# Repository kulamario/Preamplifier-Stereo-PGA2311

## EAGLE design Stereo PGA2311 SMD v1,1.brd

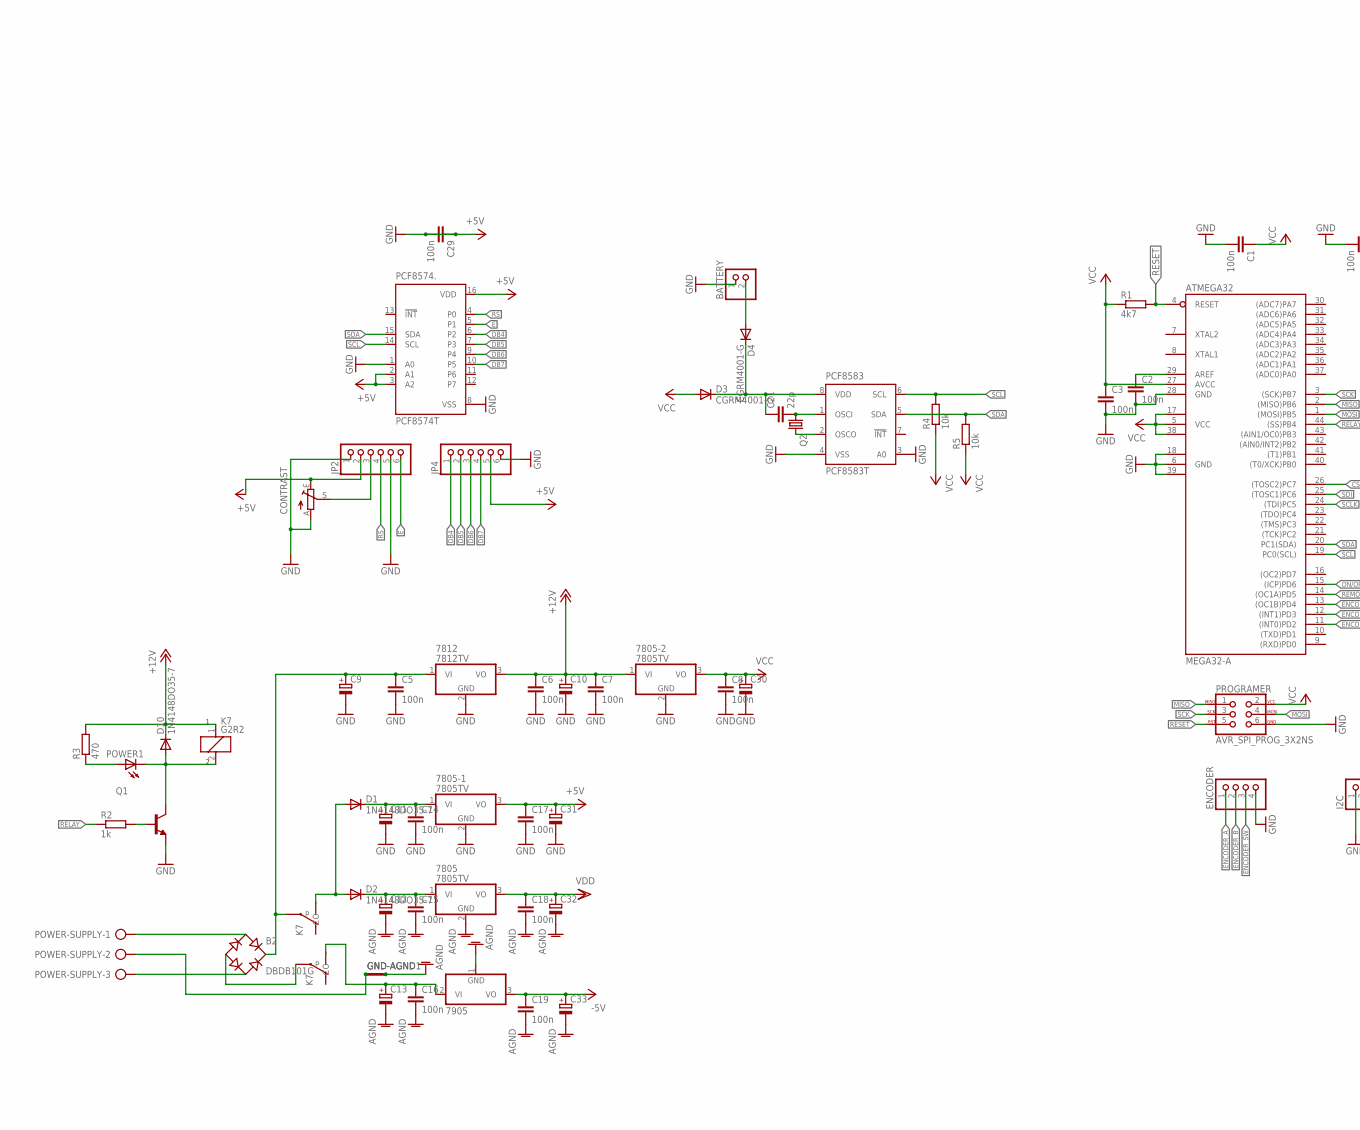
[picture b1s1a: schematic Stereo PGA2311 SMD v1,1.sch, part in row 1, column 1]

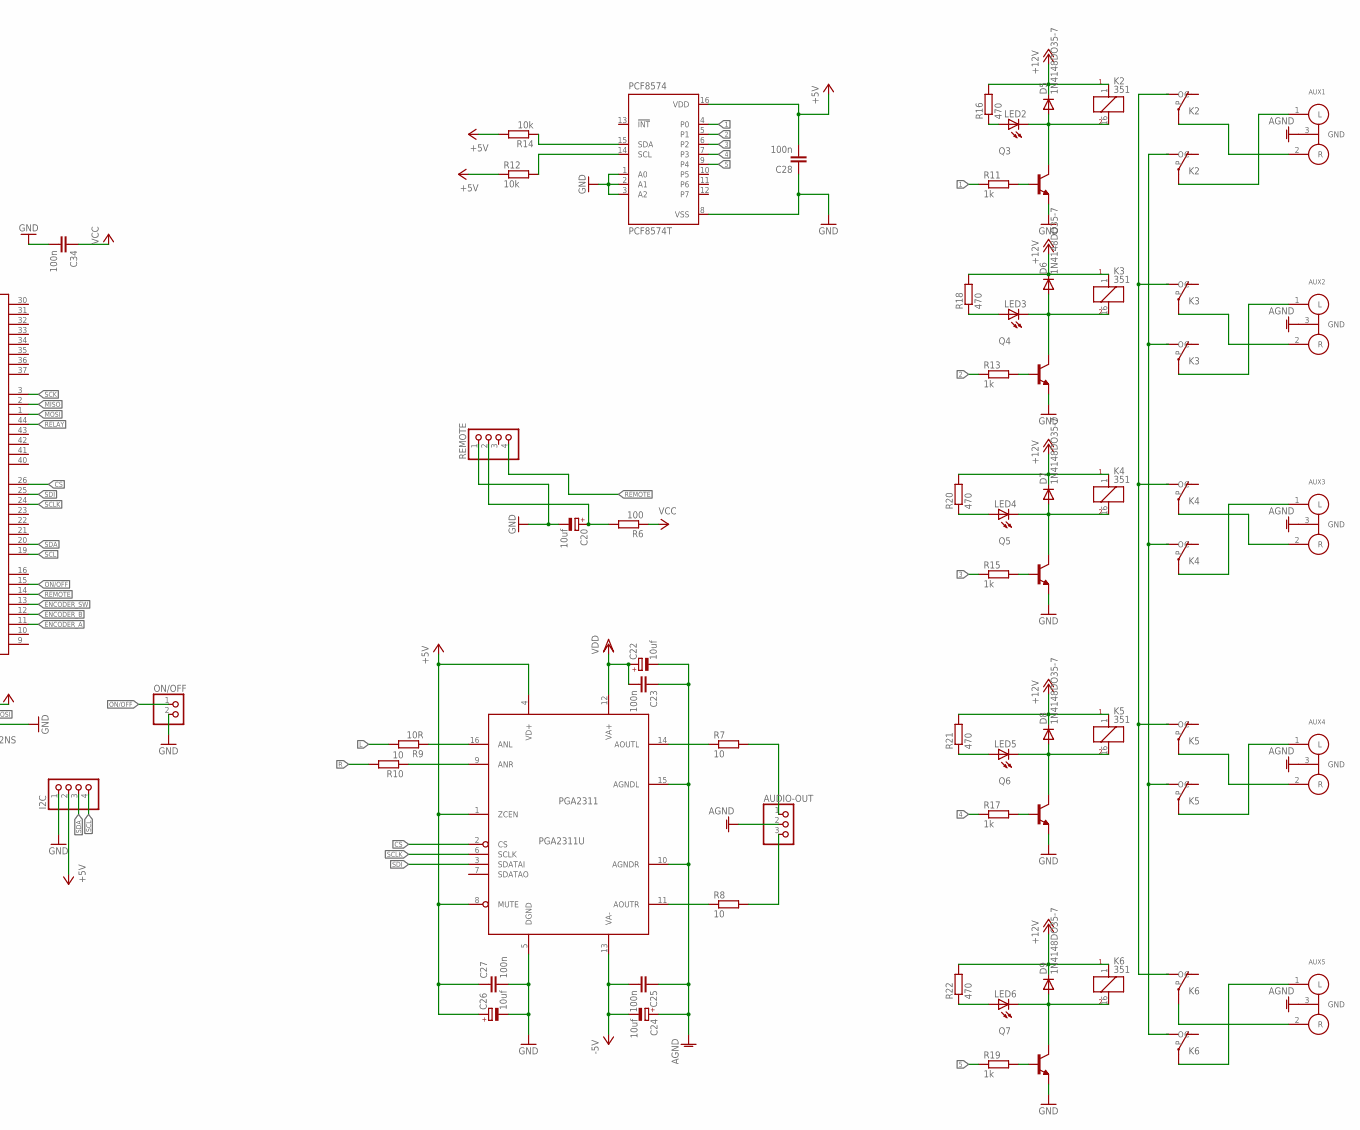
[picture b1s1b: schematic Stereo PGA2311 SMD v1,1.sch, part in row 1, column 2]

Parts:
7805, 7805-1, 7805-2: 7805TV; TO220V
7812: 7812TV; TO220V
7905: 79; TO220V
ATMEGA32: MEGA32-A; TQFP44
AUDIO-OUT: PINHD-1X3; 1X03
AUX1, AUX2, AUX3, AUX4, AUX5: RCA-EBAY
B2: DBDB101G; DB
BATTERY: PINHD-1X2; 1X02
C1: 100n; C0805
C2, C3, C23, C25, C27, C28, C29, C34: 100n; C0603
C5, C6, C7, C8, C14, C15, C16, C17, C18, C19: 100n; C025-030X050
C9, C10, C11, C12, C13, C30, C31, C32, C33: CPOL-EUE2.5-7; E2,5-7
C20: 10uf; E2-4
C21: 22p; C0603K
C22, C24, C26: 10uf; 153CLV-0505
CONTRAST: TRIM_EU-CA6V; CA6V
D1, D2, D5, D6, D7, D8, D9, D10: 1N4148DO35-7; DO35-7
D3, D4: CGRM4001-G; SOD-123_MINI-SMA
ENCODER: PINHD-1X4; 1X04
GND-AGND, GND-AGND1: SHORT-HT5; SHORT_TOP-50
I2C: PINHD-1X4; 1X04
JP2, JP4: PINHD-1X6; 1X06
K2, K3, K4, K5, K6: 351
K7: G2R2
LED2, LED3, LED4, LED5, LED6: LEDCHIPLED_0805; CHIPLED_0805
ON/OFF: PINHD-1X2; 1X02
PCF8574, PCF8574.: PCF8574T; SO16W
PCF8583: PCF8583T; SO8-7_5
PGA2311: PGA2311U; SO16-1
POWER1: LEDCHIPLED_0805; CHIPLED_0805
POWER-SUPPLY: AK300/3
PROGRAMER: AVR_SPI_PROG_3X2NS; 2X3-NS
Q1, Q3, Q4, Q5, Q6, Q7: BC547A-NPN-TO92-CBE; TO92-CBE
Q2: CRYSTALTC26H; TC26H
R1: 4k7; R0603
R2, R11, R13, R15, R17, R19: 1k; R0603
R3, R16, R18, R20, R21, R22: 470; R0603
R4, R5, R12, R14: 10k; R0603
R6: 100; R0603
R7, R8, R10: 10; R0603
R9: 10R; R0603
REMOTE: PINHD-1X4; 1X04

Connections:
1: PCF8574.4 (P0), R11.1
2: PCF8574.5 (P1), R13.1
3: PCF8574.6 (P2), R15.1
4: PCF8574.7 (P3), R17.1
5: PCF8574.9 (P4), R19.1
+5V: 7805-1.3 (VO), C17.1, C26.+, C27.1, C28.2, C29.1, C29.2, C31.+, CONTRAST.E, I2C.2, JP2.2, JP4.5, PCF8574.16 (VDD), PCF8574..2 (A1), PCF8574..3 (A2), PCF8574..16 (VDD), PGA2311.1 (ZCEN), PGA2311.4 (VD+), PGA2311.8 (MUTE), R12.1, R14.2
+12V: 7805-2.1 (VI), 7812.3 (VO), C6.1, C7.1, C10.+, D5.C, D6.C, D7.C, D8.C, D9.C, D10.C, K2.1, K3.1, K4.1, K5.1, K6.1, K7.1, R3.2, R16.2, R18.2, R20.2, R21.2, R22.2
-5V: 7905.3 (VO), C19.1, C24.-, C25.2, C33.+, PGA2311.13 (VA-)
AGND: 7805.2 (GND), 7905.1 (GND), AUDIO-OUT.2, AUX1.3 (GND), AUX2.3 (GND), AUX3.3 (GND), AUX4.3 (GND), AUX5.3 (GND), C12.-, C13.-, C15.2, C16.2, C18.2, C19.2, C22.-, C23.1, C24.+, C25.1, C32.-, C33.-, GND-AGND.2, GND-AGND1.2, PGA2311.10 (AGNDR), PGA2311.15 (AGNDL)
CS: ATMEGA32.26 ((TOSC2)PC7), PGA2311.2 (CS)
DB4: JP4.1, PCF8574..6 (P2)
DB5: JP4.2, PCF8574..7 (P3)
DB6: JP4.3, PCF8574..9 (P4)
DB7: JP4.4, PCF8574..10 (P5)
E: JP2.6, PCF8574..5 (P1)
ENCODER_A: ATMEGA32.11 ((INT0)PD2), ENCODER.1
ENCODER_B: ATMEGA32.12 ((INT1)PD3), ENCODER.2
ENCODER_SW: ATMEGA32.13 ((OC1B)PD4), ENCODER.3
GND: 7805-1.2 (GND), 7805-2.2 (GND), 7812.2 (GND), ATMEGA32.6 (GND), ATMEGA32.18 (GND1), ATMEGA32.28 (GND), ATMEGA32.39 (GND2), BATTERY.1, C1.2, C2.2, C3.2, C5.2, C6.2, C7.2, C8.2, C9.-, C10.-, C11.-, C14.2, C17.2, C20.-, C26.-, C27.2, C28.1, C30.-, C31.-, C34.2, CONTRAST.A, ENCODER.4, GND-AGND.1, GND-AGND1.1, I2C.1, JP2.1, JP2.5, JP4.6, ON/OFF.2, PCF8574.1 (A0), PCF8574.2 (A1), PCF8574.3 (A2), PCF8574.8 (VSS), PCF8574..1 (A0), PCF8574..8 (VSS), PCF8583.3 (A0), PCF8583.4 (VSS), PGA2311.5 (DGND), POWER-SUPPLY.2, PROGRAMER.6, Q1.E, Q3.E, Q4.E, Q5.E, Q6.E, Q7.E, REMOTE.1
L: K2.S2 (O), K3.S2 (O), K4.S2 (O), K5.S2 (O), K6.S2 (O), R9.2
MISO: ATMEGA32.2 ((MISO)PB6), PROGRAMER.1
MOSI: ATMEGA32.1 ((MOSI)PB5), PROGRAMER.4
unnamed: B2.AC1, POWER-SUPPLY.1
unnamed: B2.AC2, POWER-SUPPLY.3
unnamed: ATMEGA32.29 (AREF), C2.1
unnamed: C21.2, PCF8583.1 (OSCI), Q2.1
unnamed: 7812.1 (VI), B2.+, C5.1, C9.+, K7.P2
unnamed: B2.-, K7.P1
unnamed: 7905.2 (VI), C13.+, C16.1, K7.S1 (O)
unnamed: D1.A, D2.A, K7.S2 (O)
unnamed: 7805.1 (VI), C12.+, C15.1, D2.C
unnamed: 7805-1.1 (VI), C11.+, C14.1, D1.C
unnamed: D10.A, K7.2, POWER1.C, Q1.C
unnamed: Q1.B, R2.2
unnamed: PCF8583.2 (OSCO), Q2.2
unnamed: C21.1, D3.C, D4.C, PCF8583.8 (VDD)
unnamed: BATTERY.2, D4.A
unnamed: PGA2311.11 (AOUTR), R8.1
unnamed: C20.+, R6.2, REMOTE.2
unnamed: PGA2311.16 (ANL), R9.1
unnamed: PGA2311.9 (ANR), R10.1
unnamed: PGA2311.14 (AOUTL), R7.1
unnamed: D5.A, K2.16 (2), LED2.C, Q3.C
unnamed: Q3.B, R11.2
unnamed: LED2.A, R16.1
unnamed: Q4.B, R13.2
unnamed: LED3.A, R18.1
unnamed: Q5.B, R15.2
unnamed: LED4.A, R20.1
unnamed: Q6.B, R17.2
unnamed: LED5.A, R21.1
unnamed: Q7.B, R19.2
unnamed: LED6.A, R22.1
unnamed: D6.A, K3.16 (2), LED3.C, Q4.C
unnamed: AUDIO-OUT.1, R7.2
unnamed: AUDIO-OUT.3, R8.2
unnamed: AUX5.1 (L), K6.P2
unnamed: AUX5.2 (R), K6.P1
unnamed: AUX4.1 (L), K5.P2
unnamed: AUX4.2 (R), K5.P1
unnamed: AUX3.2 (R), K4.P1
unnamed: AUX3.1 (L), K4.P2
unnamed: AUX2.1 (L), K3.P2
unnamed: AUX2.2 (R), K3.P1
unnamed: AUX1.1 (L), K2.P2
unnamed: AUX1.2 (R), K2.P1
unnamed: D7.A, K4.16 (2), LED4.C, Q5.C
unnamed: D8.A, K5.16 (2), LED5.C, Q6.C
unnamed: D9.A, K6.16 (2), LED6.C, Q7.C
unnamed: POWER1.A, R3.1
unnamed: CONTRAST.S, JP2.3
ON/OFF: ATMEGA32.15 ((ICP)PD6), ON/OFF.1
R: K2.S1 (O), K3.S1 (O), K4.S1 (O), K5.S1 (O), K6.S1 (O), R10.2
RELAY: ATMEGA32.44 ((SS)PB4), R2.1
REMOTE: ATMEGA32.14 ((OC1A)PD5), REMOTE.4
RESET: ATMEGA32.4 (RESET), PROGRAMER.5, R1.2
RS: JP2.4, PCF8574..4 (P0)
SCK: ATMEGA32.3 ((SCK)PB7), PROGRAMER.3
SCL: ATMEGA32.19 (PC0(SCL)), I2C.4, PCF8574.14 (SCL), PCF8574..14 (SCL), PCF8583.6 (SCL), R4.2, R12.2
SCLK: ATMEGA32.24 ((TDI)PC5), PGA2311.6 (SCLK)
SDA: ATMEGA32.20 (PC1(SDA)), I2C.3, PCF8574.15 (SDA), PCF8574..15 (SDA), PCF8583.5 (SDA), R5.2, R14.1
SDI: ATMEGA32.25 ((TOSC1)PC6), PGA2311.3 (SDATAI)
VCC: 7805-2.3 (VO), ATMEGA32.5 (VCC), ATMEGA32.17 (VCC1), ATMEGA32.27 (AVCC), ATMEGA32.38 (VCC2), C1.1, C3.1, C8.1, C30.+, C34.1, D3.A, PROGRAMER.2, R1.1, R4.1, R5.1, R6.1
VDD: 7805.3 (VO), C18.1, C22.+, C23.2, C32.+, PGA2311.12 (VA+)

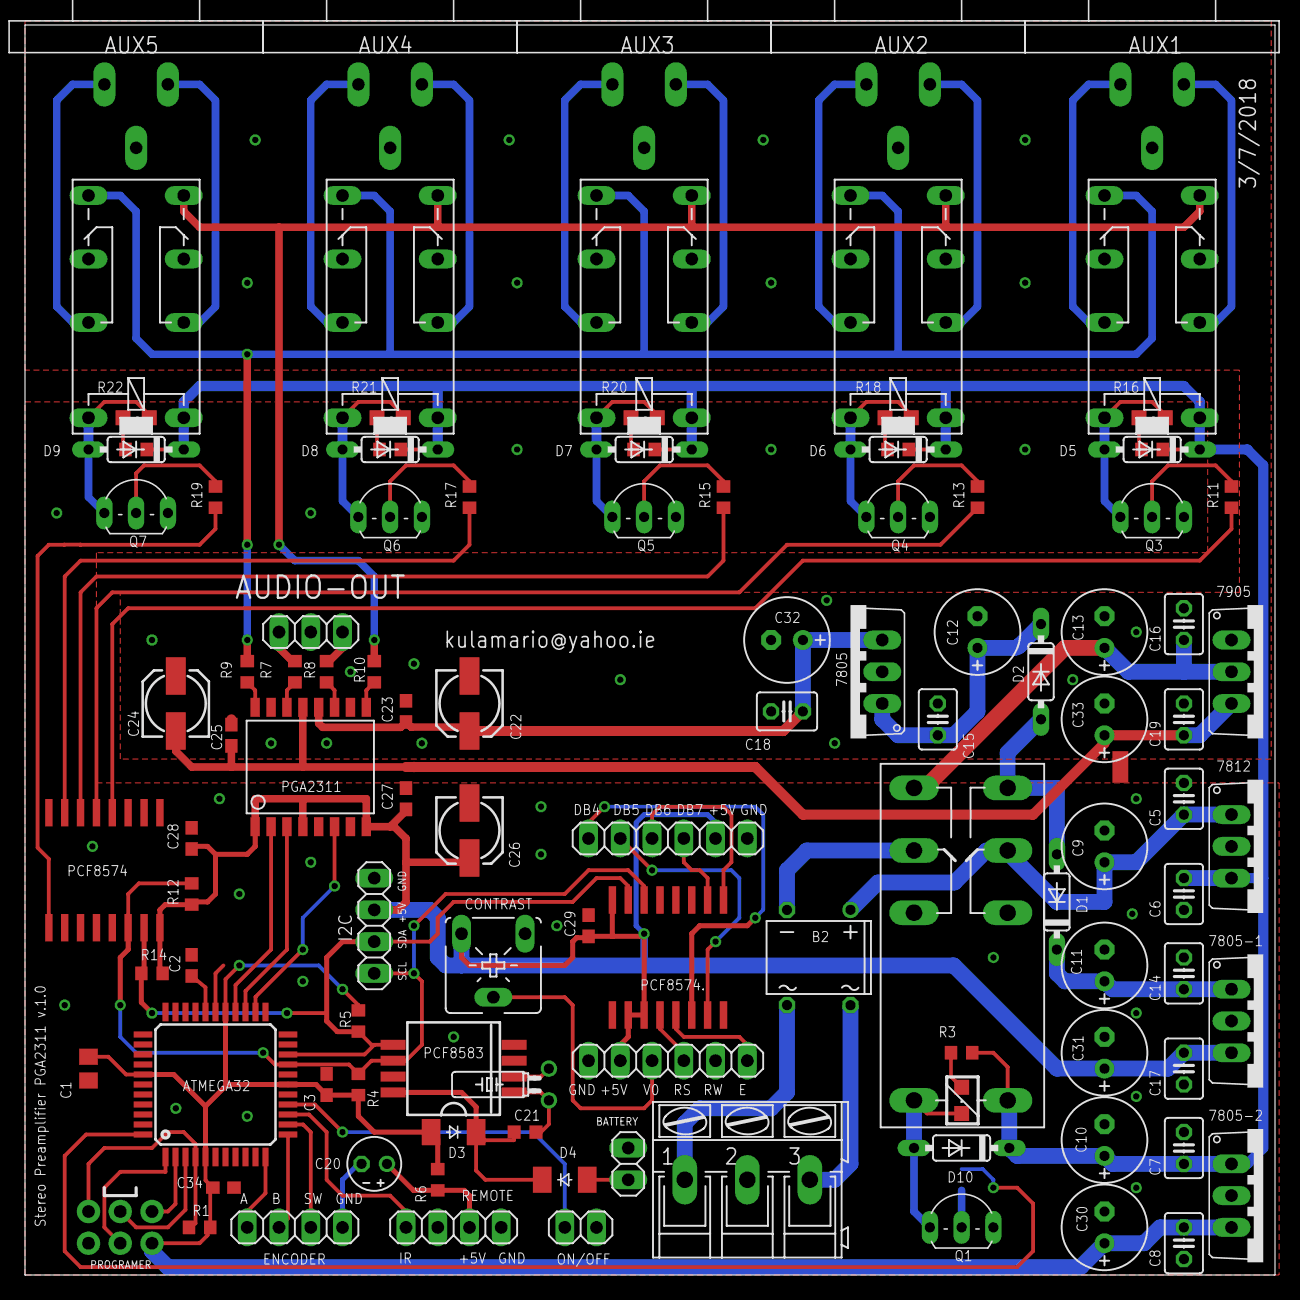
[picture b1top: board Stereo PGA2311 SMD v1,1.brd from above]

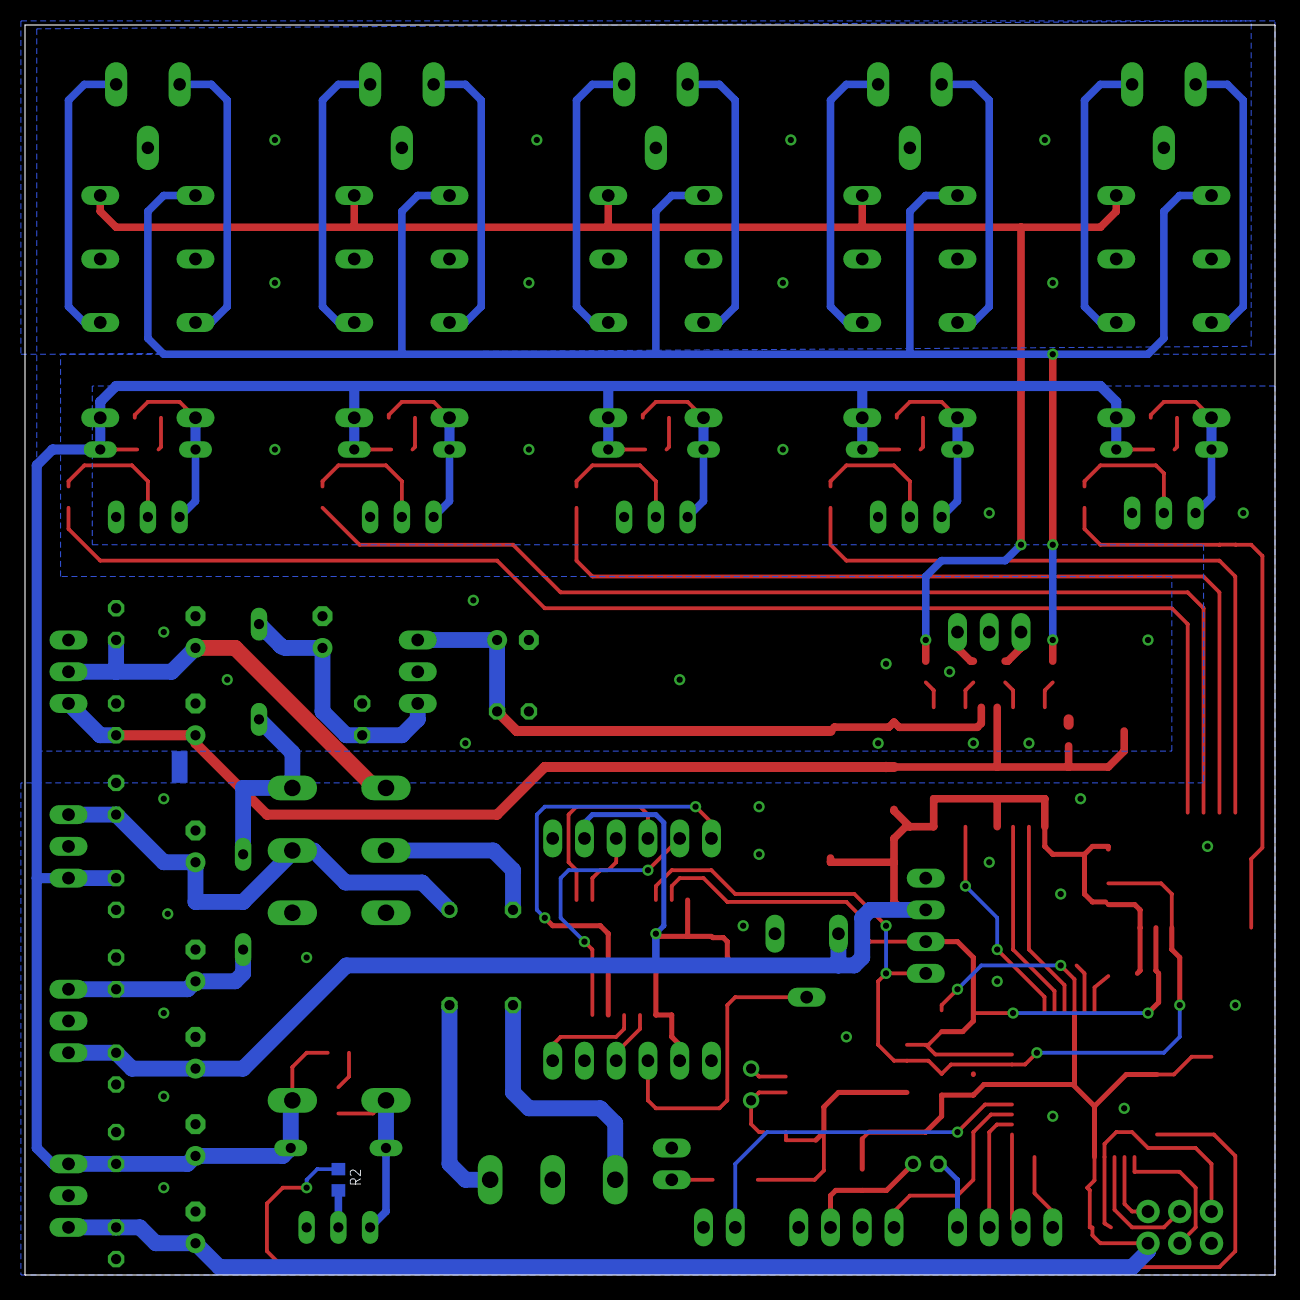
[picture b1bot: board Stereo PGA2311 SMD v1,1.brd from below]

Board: 2 copper layers, 100.0 x 100.0 mm, 113 parts (2 on the bottom side), 84 nets.

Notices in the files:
parts and their libraries:
SparkFun-Connectors: Licensing: Creative Commons ShareAlike 4.0 International - https://creativecommons.org/licenses/by-sa/4.0
